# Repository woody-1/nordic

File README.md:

# nordic nRF52832-QFxx
For growing plant and mushroom allow control of temperature and moisture in the enviroment. 
this project was designed using Kikad

It about automatisation control of humidity and temperature for plants and fungi growing
I make hardware design but not realised as a physical object.  
The project needed to finish software parts 

In my main idea, it could be used as mesh system for big rooms, and as individual sensors for smaller

I hope it will be usefull for somebody

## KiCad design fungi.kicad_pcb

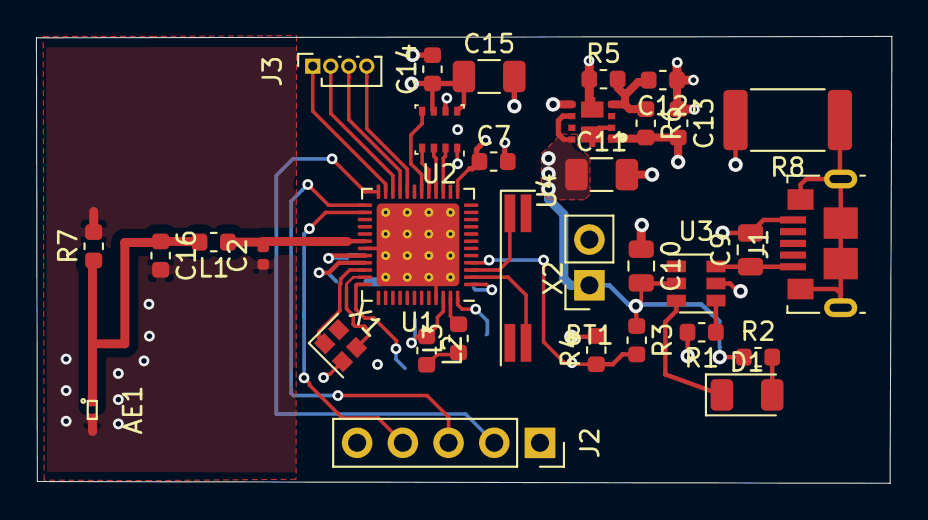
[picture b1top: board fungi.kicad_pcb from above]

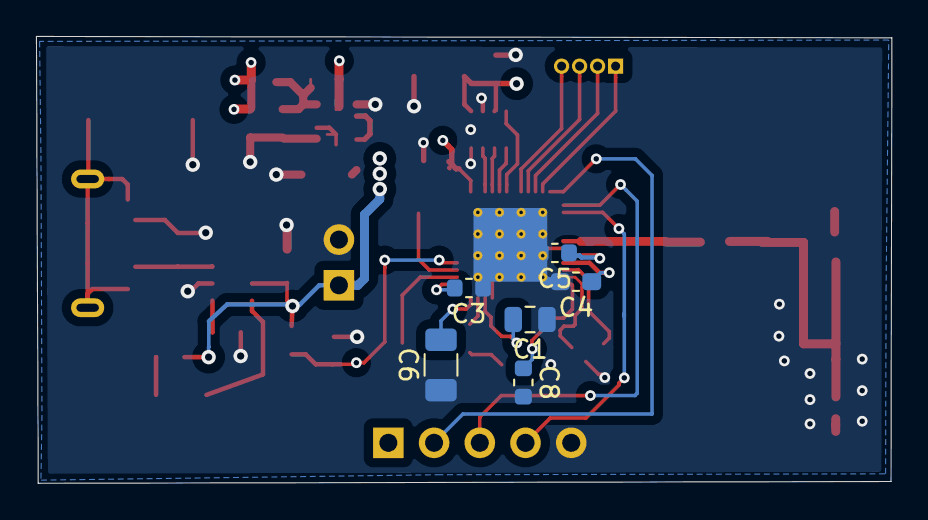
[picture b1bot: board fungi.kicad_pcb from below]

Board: 4 copper layers, 47.5 x 24.8 mm, 39 parts (6 on the bottom side), 34 nets.

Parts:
AE1: Antenna; SRCW004
BT1: Battery; PinSocket_1x02_P2.54mm_Vertical
C1: 1.0μF; C_0805_2012Metric
C2: 0.8pF; C_0402_1005Metric
C3, C14: 100nF; C_0603_1608Metric
C4: DNP; C_0603_1608Metric_Pad1.05x0.95mm_HandSolder
C5: 100pF; C_0603_1608Metric
C6: 4.7μF; C_1206_3216Metric
C7: 100 nF; C_0603_1608Metric
C8: CAP; C_0603_1608Metric
C9, C10: 1 μF; C_0805_2012Metric
C11: 4,7μF; C_1206_3216Metric
C12: 100p; C_0603_1608Metric
C13: 10μF; C_0603_1608Metric
C15: 100nF; C_1206_3216Metric
C16: CAP - запаюватися не буде; C_0603_1608Metric
D1: LED; LED_1206_3216Metric
J1: USB_B_Micro; USB_Micro-B_Molex_47346-0001
J2: Conn_01x05_Male; PinSocket_1x05_P2.54mm_Vertical
J3: Conn_01x04_Male; PinSocket_1x04_P1.00mm_Vertical
L1: 3.9nH; L_0603_1608Metric
L2: 15nH; L_0603_1608Metric
L3: 10μH; L_0603_1608Metric
R1: 0.675-10.8kOhm; R_0603_1608Metric
R2: R CHG; R_0603_1608Metric
R3, R4: 10kOhm; R_0603_1608Metric
R5: 470k; R_0603_1608Metric
R6: 150k; R_0603_1608Metric
R7: 0 ohm; R_0603_1608Metric
R8: 1 M; R_2512_6332Metric
U1: nRF52832-QFxx_own; QFN-48-1EP_6x6mm_P0.4mm_EP4.6x4.6mm_ThermalVias
U2: BME280; Bosch_LGA-8_2.5x2.5mm_P0.65mm_ClockwisePinNumbering
U3: BQ21040DBVR; SOT-23-6
U4: XCL209F083DR
X1: 32MHz; Crystal_SMD_2016-4Pin_2.0x1.6mm
X2: 32,768 kHz; Crystal_SMD_SeikoEpson_MC146-4Pin_6.7x1.5mm_HandSoldering

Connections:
/ANT50OHM: AE1.1, C16.1, L1.2, R7.1
/CS: U1.15, U2.2
/SCK: U1.17, U2.4
/SDI: U1.16, U2.3
/SDO: U1.18, U2.5
/Sheet5DAF8601/VBATMEAS: R3.2, R4.1
GND: AE1.2, BT1.2, C1.1, C2.1, C3.1, C4.2, C5.2, C6.1, C7.2, C8.2, C9.2, C10.1, C11.2, C13.2, C14.2, C15.2, C16.2, J1.5, J2.5, R1.2, R4.2, R6.2, R7.2, R8.2, U1.31, U1.45, U1.49, U2.1, U2.7, U3.5, U4.1, U4.5, X1.2
unnamed: BT1.1, C10.2, C11.1, R2.1, R3.1, U3.2, U4.6, U4.8
unnamed: C1.2, L2.1, U1.46
unnamed: C2.2, L1.1, U1.30
unnamed: C3.2, U1.1
unnamed: C4.1, U1.33
unnamed: C5.1, U1.32
unnamed: C9.1, J1.1, U3.6
unnamed: C12.2, R5.2, R6.1, U4.4
unnamed: D1.1, U3.3
unnamed: D1.2, R2.2
unnamed: J1.6, R8.1
unnamed: J2.2, U1.24
unnamed: J2.3, U1.25
unnamed: J2.4, U1.26
unnamed: J3.1, U1.23
unnamed: J3.2, U1.22
unnamed: J3.3, U1.21
unnamed: J3.4, U1.20
unnamed: L2.2, L3.1
unnamed: L3.2, U1.47
unnamed: R1.1, U3.4
unnamed: U1.2, X2.3
unnamed: U1.3, X2.1
unnamed: U1.34, X1.1
unnamed: U1.35, X1.3
unnamed: U4.2, U4.9
VDD: C6.2, C7.1, C8.1, C12.1, C13.1, C14.1, C15.1, J2.1, R5.1, U1.13, U1.36, U1.48, U2.6, U2.8, U4.10

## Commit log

2021-12-09 Nordic nRF52832 based climat control device
